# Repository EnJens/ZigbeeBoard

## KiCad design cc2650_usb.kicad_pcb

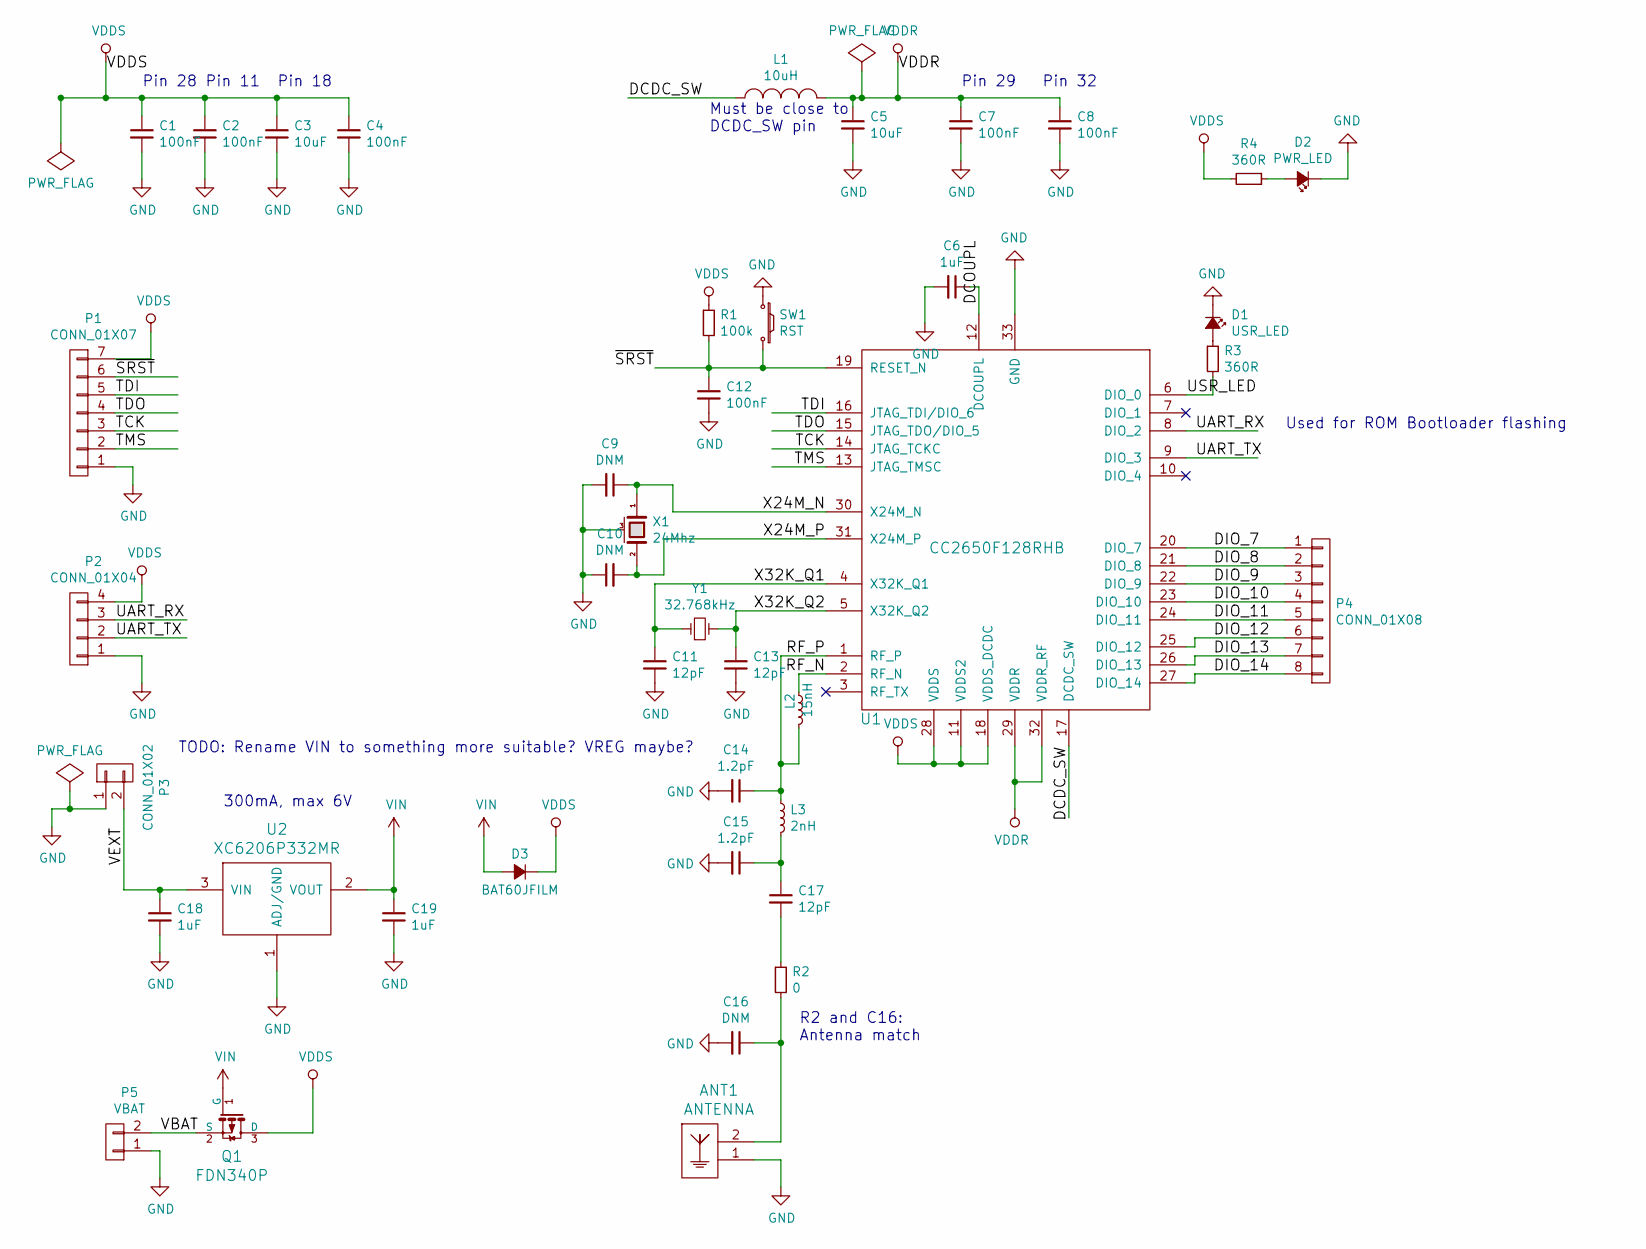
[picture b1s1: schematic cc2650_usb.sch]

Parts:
ANT1: ANTENNA; TI_DN007_2.4GHz
C1, C2, C4, C7, C8, C12: 100nF; C_0603
C3, C5: 10uF; C_0603
C6, C18, C19: 1uF; C_0603
C9, C10, C16: DNM; C_0603
C11, C13, C17: 12pF; C_0603
C14, C15: 1.2pF; C_0603
D1: USR_LED; LED_0603
D2: PWR_LED; LED_0603
D3: BAT60JFILM; SOD-323
L1: 10uH; C_0603
L2: 15nH; C_0603
L3: 2nH; C_0603
P1: CONN_01X07; Pin_Header_Straight_1x07
P2: CONN_01X04; Pin_Header_Straight_1x04
P3: CONN_01X02; Pin_Header_Straight_1x02
P4: CONN_01X08; Pin_Header_Straight_1x08
P5: VBAT; CR2032_SMD
Q1: FDN340P; SOT-23
R1: 100k; R_0603
R2: 0; R_0603
R3, R4: 360R; R_0603
SW1: RST; SmallButton
U1: CC2650F128RHB; QFN-32-1EP_5x5mm_Pitch0.5mm
U2: XC6206P332MR; SOT-23
X1: 24Mhz; crystal_FA238-TSX3225
Y1: 32.768kHz; XTAL3215

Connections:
/DCDC_SW: L1.1, U1.17 (DCDC_SW)
/DCOUPL: C6.1, U1.12 (DCOUPL)
/DIO_7: P4.1, U1.20 (DIO_7)
/DIO_8: P4.2, U1.21 (DIO_8)
/DIO_9: P4.3, U1.22 (DIO_9)
/DIO_10: P4.4, U1.23 (DIO_10)
/DIO_11: P4.5, U1.24 (DIO_11)
/DIO_12: P4.6, U1.25 (DIO_12)
/DIO_13: P4.7, U1.26 (DIO_13)
/DIO_14: P4.8, U1.27 (DIO_14)
/RF_N: L2.1, U1.2 (RF_N)
/RF_P: C14.1, L2.2, L3.1, U1.1 (RF_P)
/TCK: P1.3, U1.14 (JTAG_TCKC)
/TDI: P1.5, U1.16 (JTAG_TDI/DIO_6)
/TDO: P1.4, U1.15 (JTAG_TDO/DIO_5)
/TMS: P1.2, U1.13 (JTAG_TMSC)
/UART_RX: P2.3, U1.8 (DIO_2)
/UART_TX: P2.2, U1.9 (DIO_3)
/USR_LED: R3.2, U1.6 (DIO_0)
/VBAT: P5.2, Q1.2 (S)
/VEXT: C18.1, P3.2, U2.3 (VIN)
/X24M_N: C9.1, U1.30 (X24M_N), X1.1
/X24M_P: C10.2, U1.31 (X24M_P), X1.2
/X32K_Q1: C11.1, U1.4 (X32K_Q1), Y1.1
/X32K_Q2: C13.1, U1.5 (X32K_Q2), Y1.2
/~SRST~: C12.1, P1.6, R1.2, SW1.2, U1.19 (RESET_N)
GND: ANT1.1, C1.2, C2.2, C3.2, C4.2, C5.2, C6.2, C7.2, C8.2, C9.2, C10.1, C11.2, C12.2, C13.2, C14.2, C15.2, C16.2, C18.2, C19.2, D1.1 (K), D2.1 (K), P1.1, P2.1, P3.1, P5.1, SW1.1, U1.33 (GND), U2.1 (ADJ/GND), X1.3 (case)
unnamed: ANT1.2, C16.1, R2.2
unnamed: C15.1, C17.1, L3.2
unnamed: C17.2, R2.1
unnamed: D1.2 (A), R3.1
unnamed: D2.2 (A), R4.1
VDDR: C5.1, C7.1, C8.1, L1.2, U1.29 (VDDR), U1.32 (VDDR_RF)
VDDS: C1.1, C2.1, C3.1, C4.1, D3.1 (K), P1.7, P2.4, Q1.3 (D), R1.1, R4.2, U1.11 (VDDS2), U1.18 (VDDS_DCDC), U1.28 (VDDS)
VIN: C19.1, D3.2 (A), Q1.1 (G), U2.2 (VOUT)

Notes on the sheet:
Used for ROM Bootloader flashing
Pin 28
Pin 11
Pin 18
Must be close to DCDC_SW pin
Pin 29
Pin 32
R2 and C16: Antenna match
300mA, max 6V
TODO: Rename VIN to something more suitable? VREG maybe?

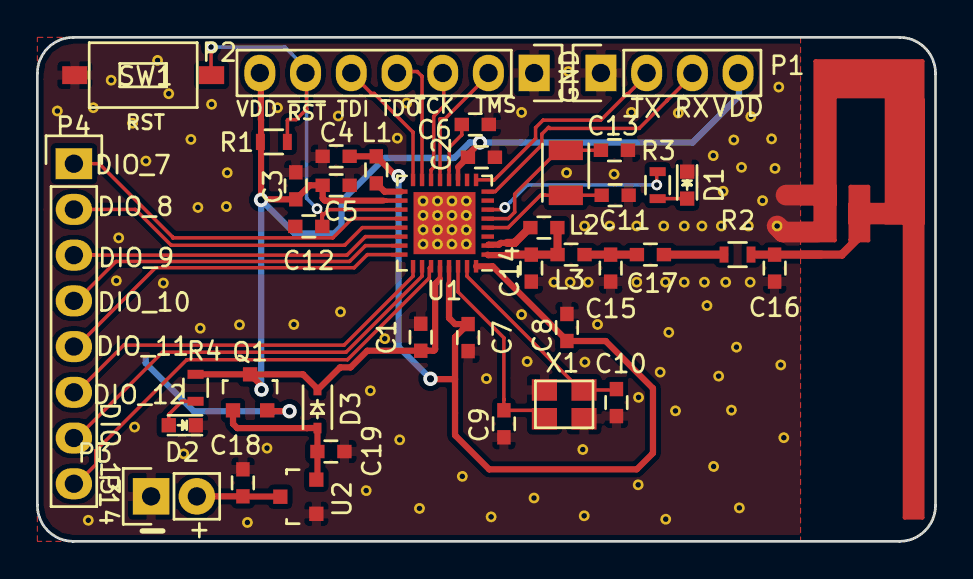
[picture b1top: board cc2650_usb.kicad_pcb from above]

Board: 2 copper layers, 49.9 x 28.0 mm, 41 parts (1 on the bottom side), 35 nets.

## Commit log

2016-08-24 First version - schematic only, no pins brought out
2016-08-27 Some layout work done
2016-08-29 Add battery input, power led, usr button & usr led, transistor/diode for power switching
2016-08-30 More routing
2016-09-02 Routing almost done
2016-09-02 More routing, remove useless TP
2016-09-02 Routing done
2016-09-02 Fully routed, fancy corners
2016-09-02 Stuff
2016-09-02 Bleh kicad
2016-09-12 All components placed (preliminary)
2016-09-18 Remove solder mask layer from antenna
2016-09-18 Fix ground plane, add more silkscreen
2016-09-18 Minor changes
